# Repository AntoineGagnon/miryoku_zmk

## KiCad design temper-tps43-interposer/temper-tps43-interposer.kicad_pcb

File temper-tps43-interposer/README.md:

# Temper TPS43 Interposer PCB

A 1.0 mm interposer that sits between the nice!nano v2 and the Temper keyboard PCB. All 24
Pro Micro pins pass straight through; four unused GPIOs plus VCC and GND are tapped out to a
6-pin 0.5 mm FFC connector for an Azoteq TPS43 trackpad. Two 0805 resistors pull up the I2C bus.

- **Board:** 20.0 x 40.0 x 1.0 mm, 2 layers, FR-4, 1 oz copper, ENIG, notched south edge
- **Toolchain:** KiCad 10
- **Status:** DRC clean, ERC clean, schematic and board verified in parity, gerbers exported

The outline is dictated by the Temper PCB, measured from `raeedcho/temper`:

| Constraint | Measurement | Consequence |
| --- | --- | --- |
| Controller header columns | X 170.43 and 185.67 | interposer centres on X 178.05 |
| Nearest choc hotswap sockets | end at X 167.49, 1.60 mm from the MCU | half-width capped at ~10.06 mm |
| Temper's right board edge | X 188.29 | 10.0 mm also stays on the board |
| nice!view header J2 | X 171.63..184.48, Y 86.33..92.16 | south edge notched to clear it |

An earlier 34 x 44 mm revision would have sat 6.4 mm over the adjacent switch column, against
choc switches that stand ~4.7 mm tall. It could not have been assembled.

## Building it

Everything is generated. Do not hand-edit `.kicad_pcb` or `.kicad_sch`: change the generator
and re-run, otherwise the next build silently throws your edits away.

```sh
./build.sh          # generate, upgrade, ERC, DRC with schematic parity
./build.sh fab      # the above plus gerbers, drill, placement, renders, and a fab zip
```

| File | Role |
| --- | --- |
| `gen_interposer.py` | Emits `temper-tps43-interposer.kicad_pcb` via the KiCad `pcbnew` Python API. Placement, routing, ground plane, silkscreen and the design rules all live here. |
| `gen_schematic.py` | Emits `temper-tps43-interposer.kicad_sch`, and owns the `COMPONENTS` table that is the single source of truth for the netlist. `gen_interposer.py` imports it, so the board and the schematic cannot drift. |
| `build.sh` | Runs both, then gates on ERC, DRC and schematic parity. |
| `PCB_SPEC.md` | The as-built design description. |

`gen_interposer.py` needs KiCad's bundled interpreter (`pcbnew` is not importable from a system
python); `build.sh` finds it. `gen_schematic.py` is plain python3.

## Pin mapping

| Pro Micro | Header pin | nRF52840 | Signal | CON1 pin | TPS43 J1 pin |
| --- | --- | --- | --- | --- | --- |
| D8 | JP1.11 | P1.04 | SDA (I2C data) | 1 | 6 |
| D9 | JP1.12 | P1.06 | SCL (I2C clock) | 2 | 5 |
| VCC | JP2.4 | 3.3 V | VDDHI | 3 | 4 |
| GND | JP1.3, JP1.4, JP2.2 | GND | GND | 4 | 3 |
| D16 | JP2.11 | P0.10 | NRST (trackpad reset) | 5 | 2 |
| D10 | JP2.12 | P0.09 | RDY (interrupt) | 6 | 1 |

The nRF numbers are from ZMK's `arduino_pro_micro_pins.dtsi` and agree with Temper's own
schematic. Earlier revisions of this file had D9, D10 and D16 wrong (P0.09 / P0.11 / P1.06),
which put the I2C clock on the wrong pin and claimed P0.11, which is actually D7, one of
Temper's matrix rows.

**These four pins are confirmed free on Temper.** Its netlist marks D0, D8, D9, D10, D14 and D16
as unconnected. Used: D1 (nice!view CS), D2 (MOSI), D3 (SCK), D4-D7 (rows), D15/D18/D19/D20/D21
(columns).

**CON1 is deliberately the mirror of the trackpad's connector.** The TPS43's own J1 pinout is
`1:RDY 2:NRST 3:GND 4:VDDHI 5:SCL 6:SDA` (Azoteq *ProxSense Standard Trackpad Module* datasheet,
revision 1.06, August 2025), and the FFC cable this board is designed around reverses the
conductor order end to end, so CON1 pin N carries TPS43 pin 7−N. See the cable warning under
[Assembly](#assembly) before you order anything.

Two things worth knowing about that pinout. First, **it changed**: the 2016 revision 1.02 PDF
still mirrored on DigiKey's media server lists TPS43 as `RDY, SDA, GND, VDDHI, SCL, NRST`, and the
revision history records v1.04 (December 2022) as "Update Figure 2-1 and Table 2-1", which is
exactly that table. Always use the copy on azoteq.com. Second, earlier revisions of this project
used a third pinout (`VDD, SDA, SCL, RDY, RST, GND`) that matches neither, and would have put
3.3 V onto RDY and shorted SCL to ground.

Every other Pro Micro pin is a plated through-hole with no copper attached to it: it connects
the nice!nano above to the Temper PCB below and nothing else.

JP1 is the left header row and JP2 the right one, viewed from the **top** of the board with the
nice!nano's USB port pointing away from you, which is the same orientation as looking down at
the nice!nano itself. The board is never flipped during assembly, so the pass-through mapping is
one to one and needs no mirroring.

CON1's two mounting tabs are tied to GND. They are the connector's only mechanical retention,
so they have to be soldered.

## Layout and routing

```
Y +23.50  board top edge
Y +22.15  CON1 courtyard, cable exits straight out over this edge
Y +21.00  CON1 signal pads (0.30 x 1.30 mm on 0.50 mm pitch)
Y +20.30  VCC bus across the top of both pull-ups
Y +20.03  escape lane A   SDA west  /  RDY east      \
Y +19.60  escape lane B   SCL west  /  RST east       >  1.50 mm corridor,
Y +19.18  escape lane C   VCC west  /  GND east      /   0.20 mm tracks
Y +18.00  R1 (SDA pull-up, X -12.00) and R2 (SCL pull-up, X -14.50)
Y +17.75  CON1 mounting tabs, tied together and dropped to the ground plane
Y +12.70  header pin 1
Y -15.24  header pin 12
Y -20.50  board bottom edge
```

The six FFC pads escape south through the corridor between the pad row and the mounting tabs,
three lanes to each side. Each lane holds its own Y until it reaches its own trunk X and then
turns square: a lane that dove diagonally toward its trunk would clip the corner off the lane
below it, and 0.425 mm of lane spacing leaves no room for that.

The lane order is not a choice. The pad nearest the centre has to take the innermost lane so it
can duck under its neighbours' drops, and a lane turning south then blocks every lane below it
from reaching further out. So lane A turns furthest from the centre and lane C nearest to it, and
whichever net lands on lane C is boxed in. Here that is VCC on the west side and GND on the east,
which is convenient: GND only needs to reach the plane, and VCC has to cross the board anyway.

Trunk positions: SDA −9.50, SCL −6.30, VCC −5.00, GND +4.60, RST +5.40, RDY +6.30. SDA runs
*outside* the JP1 pad column rather than in the centre channel, which is what puts the two pull-up
resistors within reach of it.

Six vias, each earning its place:

- **VCC** (2 vias) drops to B.Cu at the corridor exit because lane C cannot travel on F.Cu at
  all, then crosses to JP2.4 and spurs back up to the pull-up bus.
- **SCL** (2 vias) reaches R2 with a B.Cu hop under the SDA trunk and the JP1 pad column.
- **RST** (1 via) hops under the RDY trunk. RDY has the outer trunk, so it must serve the more
  southern header pin or the inner trunk's jog would cut across it. That would otherwise force
  RDY and RST to swap header pins, and this via is what keeps the ZMK overlay untouched.
- **CON1's mounting tabs** (1 via) drop to the ground plane under the connector body, picking up
  the GND escape lane on the way.

B.Cu is otherwise a single 1283 mm2 GND pour with thermal reliefs on the through-hole GND pads,
which also gives the whole I2C run a reference plane underneath. JP1.3, JP1.4 and JP2.2 pick up
GND from the plane, so no ground track has to thread past a header column.

Design rules, all enforced by `build.sh`: 0.20 mm minimum track and clearance, 0.60/0.30 mm
vias, 0.30 mm minimum hole, 0.40 mm copper-to-edge. The tightest feature on the board is the
connector escape: 0.20 mm tracks on 0.40 mm centres. Comfortably inside any cheap 2-layer
process, but it is the number to check if a fab quotes looser capabilities.

## BOM

See `BOM.md` for links and prices.

| Qty | Designator | Part | Footprint |
| --- | --- | --- | --- |
| 2 | JP1, JP2 | 1x12 through-hole positions, 2.54 mm | `PinHeader_1x12_P2.54mm_Vertical` |
| 1 | CON1 | Hirose FH12-6S-0.5SH, 6-pos 0.5 mm FFC, horizontal | `Hirose_FH12-6S-0.5SH_1x06-1MP_P0.50mm_Horizontal` |
| 2 | R1, R2 | 2.2 kOhm 0805 thick film | `R_0805_2012Metric` |
| 24 | - | **Mill-Max pins** (bottom side, into Temper's sockets) | - |
| 24 | - | **Mill-Max 310 series machine sockets** (top side, for the nice!nano) | - |
| 1 | - | 6-pos 0.5 mm FFC cable, ~50 mm | - |
| 1 | - | Azoteq TPS43-201A-S trackpad module | - |

**Do not use ordinary 2.54 mm breakaway headers here.** Temper is built with Mill-Max 310 series
machine sockets, whose bore takes ~0.5 mm round pins. Standard header pins are 0.64 mm square and
will not fit; forcing them wrecks the socket. The interposer needs Mill-Max pins on the bottom to
plug into Temper, and Mill-Max 310 sockets on top because the nice!nano already has Mill-Max pins
soldered to it. The 1.0 mm holes in this footprint suit both.

CON1 replaces the Molex 503480-0600 called for in earlier revisions. The Molex part's land
pattern was never verified against its datasheet here, and the footprint that shipped with it
used non-plated holes for mounting, which gives a 0.5 mm-pitch connector no solder retention at
all. The Hirose part ships as a datasheet-derived footprint in KiCad's own `Connector_FFC-FPC`
library and has two 1.8 x 2.2 mm SMT solder tabs.

## Assembly

The board is oriented so that the nice!nano ends up on top:

1. **Top side:** solder 24 **Mill-Max 310 machine sockets** at JP1 and JP2. These receive the
   Mill-Max pins already soldered to your nice!nano.
2. **Bottom side:** solder 24 **Mill-Max pins**, pointing down, to plug into Temper's own
   sockets. Not square breakaway header pins, see the BOM note.
3. **Top side:** solder CON1. Both mounting tabs must be soldered; they are the only thing
   holding it on. The cable opening faces the top edge of the board, away from the nice!nano.
4. **Top side:** solder R1 and R2.
5. Unplug the nice!nano from Temper, plug the interposer into Temper's sockets, then plug the
   nice!nano into the interposer.
6. Connect the TPS43 with the FFC cable. It runs straight out over the top edge toward the
   thumb cluster, with no fold, and never passes under the nice!nano.

### Verify the cable before you fab this board

CON1 is wired for a cable that **reverses** the conductor order, so that CON1 pin N reaches
TPS43 J1 pin 7−N. If your cable is straight-through instead, this board is wrong and every signal
is scrambled: 3.3 V would land on the trackpad's RDY pin.

Do not trust the "Type A" / "Type B" label. The naming is not standardised. DigiKey and Molex
call same-side contacts Type A and opposite-side Type D; other vendors call the same thing Type B,
Type 1 or Type 2. FH12-6S-0.5SH is bottom-contact, so at the interposer end the conductors face
down toward the board, but that alone does not tell you the mapping.

**Check it with a meter.** Lay the cable out as it will actually run between the two boards, then
ring out conductor 1 at one end against each conductor at the other:

- continuity from end-A conductor 1 to end-B conductor **6** confirms reversed: this board is
  correct as fabbed
- continuity from end-A conductor 1 to end-B conductor **1** means straight-through: **do not
  fab this board**, see below

CON1's pinout is derived in `gen_schematic.py` from `TPS43_J1` (the datasheet table) and
`CON1_MIRRORED` (the cable's mapping), so the relationship is explicit rather than a magic
constant. Setting `CON1_MIRRORED = False` produces the correct *netlist* for a straight-through
cable, but it is not a drop-in change and the generator will refuse to route it: flipping the
cable flips the escape-lane order, which moves the pull-ups to the east side and swaps which
header column carries I2C, so the ZMK overlay changes too. `route()`, the trunk constants and the
resistor placement have to be redone together. The assertion tells you exactly that if you try.

**Check the USB-C clearance before ordering.** CON1 spans Y +14.25 to +22.15, directly in front
of the nice!nano's USB-C port. Mill-Max sockets lift the module only ~2 mm and the FH12 is about
2 mm tall, so this is tighter than it would be with tall sockets. Measure it.

**Temper's battery pads sit under the nice!nano** (BT1, X 173.62..182.83, Y 57.82..63.08), and
the assembly guide has you solder battery wires there. The interposer's B.Cu ground pour will end
up directly over that wiring with only the socket standoff in between. Dress the wires flat and
check for chafing before seating the interposer.

## Ordering the PCB

Upload `output/temper-tps43-interposer-gerbers.zip`, or the `.kicad_pcb` directly if the fab
accepts it.

- Layers: 2
- Thickness: 1.0 mm
- Surface finish: **ENIG** (recommended: the 0.5 mm FFC pads are fine pitch)
- Copper weight: 1 oz
- Minimum track / clearance required: 0.20 mm / 0.20 mm
- Minimum drill: 0.30 mm

## ZMK firmware

The pin assignment above is exactly what the original design specified, so the overlay is
unchanged.

### `config/temper_right.conf`

```
CONFIG_INPUT_TPS43=y
CONFIG_I2C=y
CONFIG_ZMK_POINTING=y
CONFIG_NFCT_PINS_AS_GPIOS=y
```

`CONFIG_NFCT_PINS_AS_GPIOS=y` is **required**, not optional. RDY lands on D10 = P0.09 and the
trackpad reset on D16 = P0.10, and those two are the nRF52840's NFC antenna pins. Without this
they are not GPIOs and neither signal works.

### `config/temper_right.overlay`

```dts
#include "temper.dtsi"

&default_transform {
    col-offset = <5>;
};

&kscan0 {
    col-gpios
        = <&pro_micro 15 GPIO_ACTIVE_HIGH>
        , <&pro_micro 18 GPIO_ACTIVE_HIGH>
        , <&pro_micro 19 GPIO_ACTIVE_HIGH>
        , <&pro_micro 20 GPIO_ACTIVE_HIGH>
        , <&pro_micro 21 GPIO_ACTIVE_HIGH>
        ;
};

/* I2C on D8(SDA) / D9(SCL), a separate bus from the nice!view SPI on D1/D2/D3.
 * D8 = P1.04 and D9 = P1.06. Earlier revisions of this file said D9 = P0.09, which is
 * wrong: P0.09 is D10. Verified against ZMK's arduino_pro_micro_pins.dtsi and against
 * Temper's own schematic symbol pin names. */
&pinctrl {
    i2c1_default: i2c1_default {
        group1 {
            psels = <NRF_PSEL(TWIM_SDA, 1, 4)>,
                    <NRF_PSEL(TWIM_SCL, 1, 6)>;
        };
    };
    i2c1_sleep: i2c1_sleep {
        group1 {
            psels = <NRF_PSEL(TWIM_SDA, 1, 4)>,
                    <NRF_PSEL(TWIM_SCL, 1, 6)>;
            low-power-enable;
        };
    };
};

&i2c1 {
    compatible = "nordic,nrf-twim";
    status = "okay";
    clock-frequency = <I2C_BITRATE_FAST>;
    pinctrl-0 = <&i2c1_default>;
    pinctrl-1 = <&i2c1_sleep>;
    pinctrl-names = "default", "sleep";

    tps43: trackpad@74 {
        compatible = "azoteq,tps43";
        reg = <0x74>;
        rdy-gpios = <&pro_micro 10 GPIO_ACTIVE_HIGH>;
        rst-gpios = <&pro_micro 16 GPIO_ACTIVE_HIGH>;
        enable-power-management;
        scroll;
        two-finger-tap;
        single-tap;
        press-and-hold;
    };
};

/ {
    split_inputs {
        #address-cells = <1>;
        #size-cells = <0>;
        tps43_split: tps43_split@0 {
            compatible = "zmk,input-split";
            reg = <0>;
            device = <&tps43>;
        };
    };
};
```

The `rdy-gpios` and `rst-gpios` numbers go through the `pro_micro` nexus, so they are correct as
written regardless of the nRF pin numbering.

### Central (left) side

```dts
/ {
    split_inputs {
        #address-cells = <1>;
        #size-cells = <0>;
        tps43_split: tps43_split@0 {
            compatible = "zmk,input-split";
            reg = <0>;
        };
    };
    tps43_listener: tps43_listener {
        compatible = "zmk,input-listener";
        device = <&tps43_split>;
        status = "okay";
    };
};
```

### Build workflow

Add `stelmakhdigital/zmk_driver_azoteq` as an external module in the GitHub Actions build
workflow's `modules` matrix variable.

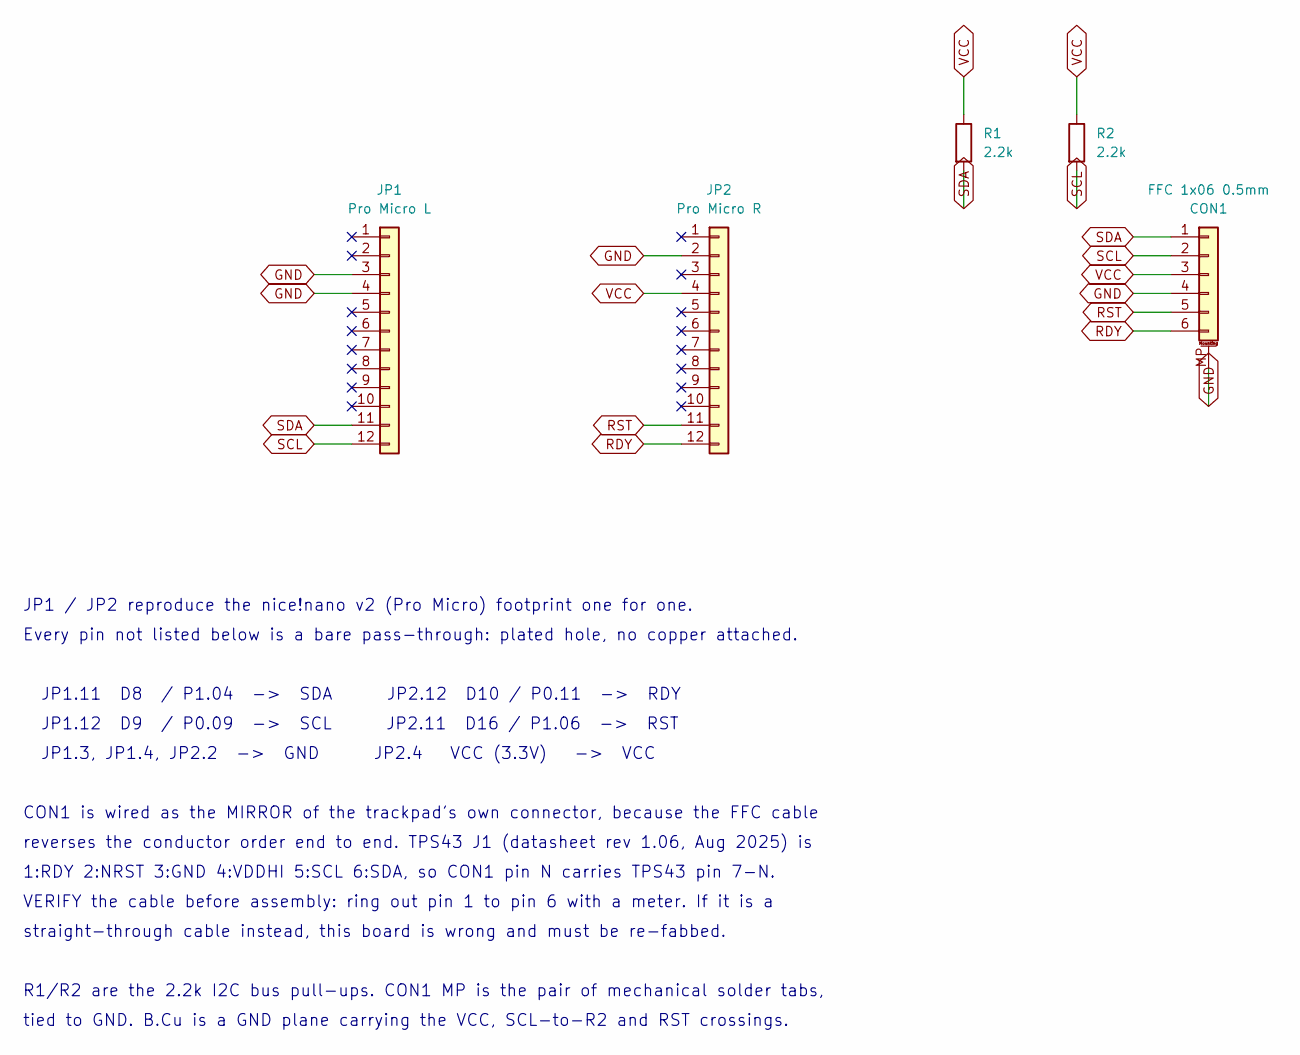
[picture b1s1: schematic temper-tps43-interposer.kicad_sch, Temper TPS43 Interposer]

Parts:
CON1: FFC 1x06 0.5mm; Hirose_FH12-6S-0.5SH_1x06-1MP_P0.50mm_Horizontal
JP1: Pro Micro L; PinHeader_1x12_P2.54mm_Vertical
JP2: Pro Micro R; PinHeader_1x12_P2.54mm_Vertical
R1, R2: 2.2k; R_0805_2012Metric

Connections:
GND: CON1.4, CON1.MP (MountPin), JP1.3, JP1.4, JP2.2
RDY: CON1.6, JP2.12
RST: CON1.5, JP2.11
SCL: CON1.2, JP1.12, R2.2
SDA: CON1.1, JP1.11, R1.2
VCC: CON1.3, JP2.4, R1.1, R2.1

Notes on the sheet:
JP1.12 D9 / P0.09 -> SCL JP2.11 D16 / P1.06 -> RST
VERIFY the cable before assembly: ring out pin 1 to pin 6 with a meter. If it is a
JP1.3, JP1.4, JP2.2 -> GND JP2.4 VCC (3.3V) -> VCC
R1/R2 are the 2.2k I2C bus pull-ups. CON1 MP is the pair of mechanical solder tabs,
JP1.11 D8 / P1.04 -> SDA JP2.12 D10 / P0.11 -> RDY
JP1 / JP2 reproduce the nice!nano v2 (Pro Micro) footprint one for one.
reverses the conductor order end to end. TPS43 J1 (datasheet rev 1.06, Aug 2025) is
CON1 is wired as the MIRROR of the trackpad's own connector, because the FFC cable
1:RDY 2:NRST 3:GND 4:VDDHI 5:SCL 6:SDA, so CON1 pin N carries TPS43 pin 7-N.
Every pin not listed below is a bare pass-through: plated hole, no copper attached.
straight-through cable instead, this board is wrong and must be re-fabbed.
tied to GND. B.Cu is a GND plane carrying the VCC, SCL-to-R2 and RST crossings.

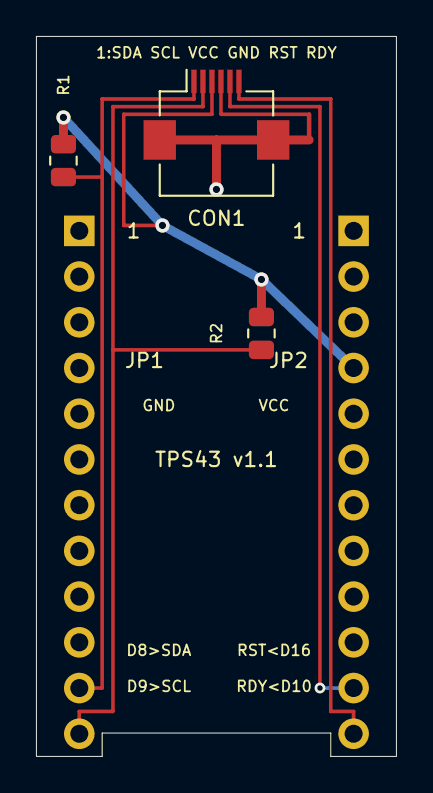
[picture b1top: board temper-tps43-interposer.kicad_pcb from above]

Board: 2 copper layers, 20.0 x 40.0 mm, 5 parts (0 on the bottom side), 6 nets.

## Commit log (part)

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2025-10-20 Add GitHub Actions folder organization config
    This config file enables the GitHub Actions Folder Organizer extension
    to organize workflows into logical folders:
    - Build Examples
    - Build Process
    - Testing
2025-10-20 Move config to .github/actions-folders.json
    - Move from .github/workflows/actions-folders.yml to .github/actions-folders.json
    - Prevents GitHub Actions from treating config as workflow
    - Switch from YAML to JSON format for simpler parsing
2025-10-24 Add command to run GitHub workflow for build inputs
